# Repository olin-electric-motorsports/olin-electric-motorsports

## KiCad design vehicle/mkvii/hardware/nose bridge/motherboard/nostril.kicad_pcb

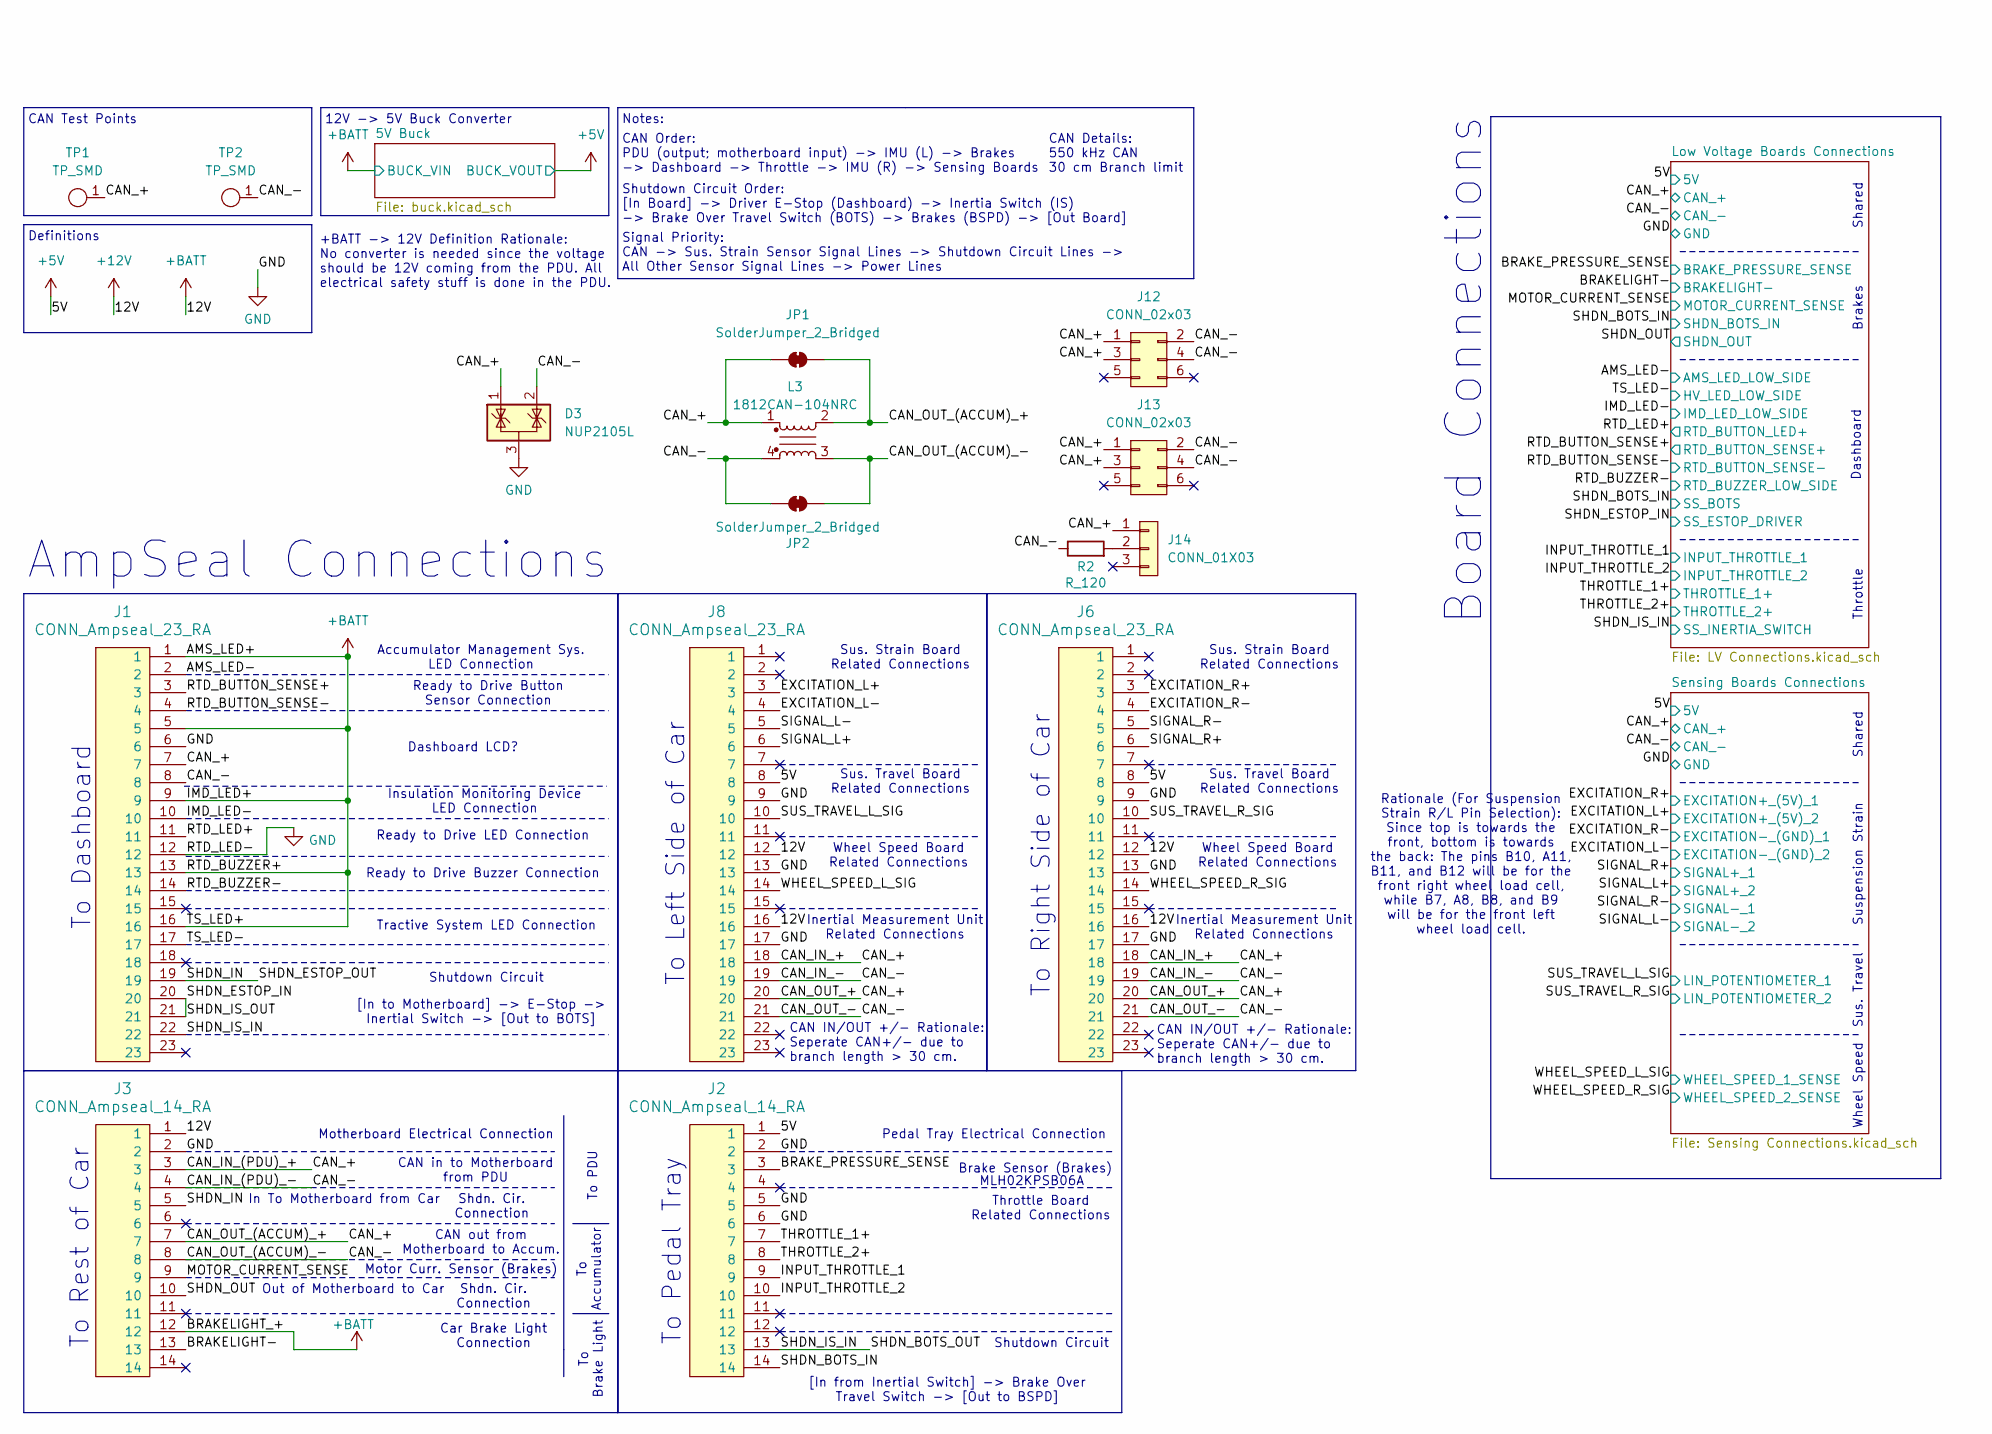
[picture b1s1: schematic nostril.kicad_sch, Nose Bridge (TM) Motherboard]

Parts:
D3: NUP2105L; SOT-23
J1, J6, J8: CONN_Ampseal_23_RA; Ampseal_23_RA; MPN 776087-1
J2, J3: CONN_Ampseal_14_RA; Ampseal_14_RA; MPN 1-776266-1
J12, J13: CONN_02x03; PinHeader_2x03_P2.54mm_Vertical; MPN 10129381-906002BLF
J14: CONN_01X03; PinHeader_1x03_P2.54mm_Vertical; MPN PH1-03-UA
JP1, JP2: SolderJumper_2_Bridged; SolderJumper-2_P1.3mm_Bridged2Bar_Pad1.0x1.5mm
L3: 1812CAN-104NRC; L_CommonModeChoke_Coilcraft_1812CAN
R2: R_120; R_0603; MPN RC0603FR-13120RL
TP1, TP2: TP_SMD; Test_Point_SMD; MPN 5019

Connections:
+5V: J2.1, J6.8, J8.8; also elsewhere on the board
/AMS_LED-: J1.2; also elsewhere on the board
/BRAKELIGHT-: J3.13; also elsewhere on the board
/BRAKE_PRESSURE_SENSE: J2.3; also elsewhere on the board
/CAN_+: D3.1 (K), J1.7, J3.3, J3.7, J6.18, J6.20, J8.18, J8.20, J12.1, J12.3, J13.1, J13.3, J14.1, JP1.1 (A), JP1.2 (B), L3.1, L3.2, TP1.1; also elsewhere on the board
/CAN_-: D3.2 (K), J1.8, J3.4, J3.8, J6.19, J6.21, J8.19, J8.21, J12.2, J12.4, J13.2, J13.4, JP2.1 (A), JP2.2 (B), L3.3, L3.4, R2.1, TP2.1; also elsewhere on the board
/EXCITATION_L+: J8.3; also elsewhere on the board
/EXCITATION_L-: J8.4; also elsewhere on the board
/EXCITATION_R+: J6.3; also elsewhere on the board
/EXCITATION_R-: J6.4; also elsewhere on the board
/IMD_LED-: J1.10; also elsewhere on the board
/INPUT_THROTTLE_1: J2.9; also elsewhere on the board
/INPUT_THROTTLE_2: J2.10; also elsewhere on the board
/MOTOR_CURRENT_SENSE: J3.9; also elsewhere on the board
/RTD_BUTTON_SENSE+: J1.3; also elsewhere on the board
/RTD_BUTTON_SENSE-: J1.4; also elsewhere on the board
/RTD_BUZZER-: J1.14; also elsewhere on the board
/RTD_LED+: J1.11; also elsewhere on the board
/SHDN_BOTS_IN: J2.14; also elsewhere on the board
/SHDN_BOTS_OUT: J1.22, J2.13; also elsewhere on the board
/SHDN_ESTOP_IN: J1.20, J1.21; also elsewhere on the board
/SHDN_ESTOP_OUT: J1.19, J3.5
/SHDN_OUT: J3.10; also elsewhere on the board
/SIGNAL_L+: J8.6; also elsewhere on the board
/SIGNAL_L-: J8.5; also elsewhere on the board
/SIGNAL_R+: J6.6; also elsewhere on the board
/SIGNAL_R-: J6.5; also elsewhere on the board
/SUS_TRAVEL_L_SIG: J8.10; also elsewhere on the board
/SUS_TRAVEL_R_SIG: J6.10; also elsewhere on the board
/THROTTLE_1+: J2.7; also elsewhere on the board
/THROTTLE_2+: J2.8; also elsewhere on the board
/TS_LED-: J1.17; also elsewhere on the board
/WHEEL_SPEED_L_SIG: J8.14; also elsewhere on the board
/WHEEL_SPEED_R_SIG: J6.14; also elsewhere on the board
GND: D3.3 (A), J1.6, J1.12, J2.2, J2.5, J2.6, J3.2, J6.9, J6.13, J6.17, J8.9, J8.13, J8.17; also elsewhere on the board
unnamed: J14.2, R2.2

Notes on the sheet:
Sus. Strain Board Related Connections
Inertial Measurement Unit Related Connections
CAN Order: PDU (output; motherboard input) -> IMU (L) -> Brakes -> Dashboard -> Throttle -> IMU (R) -> Sensing Boards
Shdn. Cir. Connection
Tractive System LED Connection
Insulation Monitoring Device LED Connection
Shutdown Circuit Order: [In Board] -> Driver E-Stop (Dashboard) -> Inertia Switch (IS) -> Brake Over Travel Switch (BOTS) -> Brakes (BSPD) -> [Out Board]
Signal Priority: CAN -> Sus. Strain Sensor Signal Lines -> Shutdown Circuit Lines -> All Other Sensor Signal Lines -> Power Lines
Wheel Speed Board Related Connections
In To Motherboard from Car
Throttle Board Related Connections
Brake Sensor (Brakes)
Shutdown Circuit
Sus. Travel Board Related Connections
[In from Inertial Switch] -> Brake Over Travel Switch -> [Out to BSPD]
Dashboard
CAN Test Points
Motherboard Electrical Connection
Accumulator Management Sys. LED Connection
To Accumulator
CAN Details: 550 kHz CAN 30 cm Branch limit
Wheel Speed
Ready to Drive Buzzer Connection
CAN IN/OUT +/- Rationale: Seperate CAN+/- due to branch length > 30 cm.
To Brake Light
Dashboard LCD?
To Right Side of Car
Definitions
Motor Curr. Sensor (Brakes)
Shared
Ready to Drive Button Sensor Connection
Out of Motherboard to Car
+BATT -> 12V Definition Rationale: No converter is needed since the voltage should be 12V coming from the PDU. All electrical safety stuff is done in the PDU.
MLH02KPSB06A
Throttle
Car Brake Light Connection
To PDU
CAN out from Motherboard to Accum.
12V -> 5V Buck Converter
Notes:

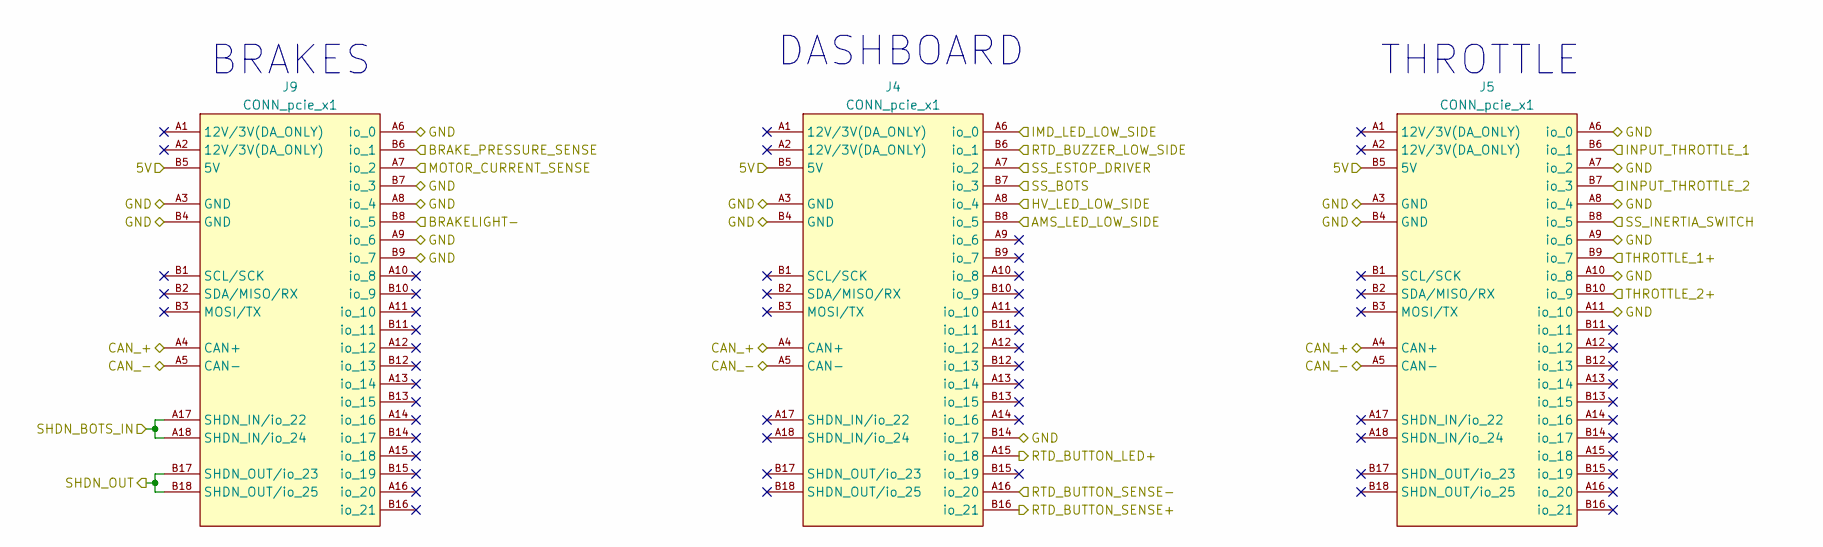
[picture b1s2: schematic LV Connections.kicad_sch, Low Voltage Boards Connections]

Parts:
J4, J5, J9: CONN_pcie_x1; te_pcie_x1_connector

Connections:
+5V: J4.B5 (5V), J5.B5 (5V), J9.B5 (5V); also elsewhere on the board
/AMS_LED-: J4.B8 (io_5); also elsewhere on the board
/BRAKELIGHT-: J9.B8 (io_5); also elsewhere on the board
/BRAKE_PRESSURE_SENSE: J9.B6 (io_1); also elsewhere on the board
/CAN_+: J4.A4 (CAN+), J5.A4 (CAN+), J9.A4 (CAN+); also elsewhere on the board
/CAN_-: J4.A5 (CAN-), J5.A5 (CAN-), J9.A5 (CAN-); also elsewhere on the board
/IMD_LED-: J4.A6 (io_0); also elsewhere on the board
/INPUT_THROTTLE_1: J5.B6 (io_1); also elsewhere on the board
/INPUT_THROTTLE_2: J5.B7 (io_3); also elsewhere on the board
/MOTOR_CURRENT_SENSE: J9.A7 (io_2); also elsewhere on the board
/RTD_BUTTON_SENSE+: J4.B16 (io_21); also elsewhere on the board
/RTD_BUTTON_SENSE-: J4.A16 (io_20); also elsewhere on the board
/RTD_BUZZER-: J4.B6 (io_1); also elsewhere on the board
/RTD_LED+: J4.A15 (io_18); also elsewhere on the board
/SHDN_BOTS_IN: J4.B7 (io_3), J9.A17 (SHDN_IN/io_22), J9.A18 (SHDN_IN/io_24); also elsewhere on the board
/SHDN_BOTS_OUT: J5.B8 (io_5); also elsewhere on the board
/SHDN_ESTOP_IN: J4.A7 (io_2); also elsewhere on the board
/SHDN_OUT: J9.B17 (SHDN_OUT/io_23), J9.B18 (SHDN_OUT/io_25); also elsewhere on the board
/THROTTLE_1+: J5.B9 (io_7); also elsewhere on the board
/THROTTLE_2+: J5.B10 (io_9); also elsewhere on the board
/TS_LED-: J4.A8 (io_4); also elsewhere on the board
GND: J4.A3 (GND), J4.B4 (GND), J4.B14 (io_17), J5.A3 (GND), J5.A6 (io_0), J5.A7 (io_2), J5.A8 (io_4), J5.A9 (io_6), J5.A10 (io_8), J5.A11 (io_10), J5.B4 (GND), J9.A3 (GND), J9.A6 (io_0), J9.A8 (io_4), J9.A9 (io_6), J9.B4 (GND), J9.B7 (io_3), J9.B9 (io_7); also elsewhere on the board

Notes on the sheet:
BRAKES
DASHBOARD
THROTTLE

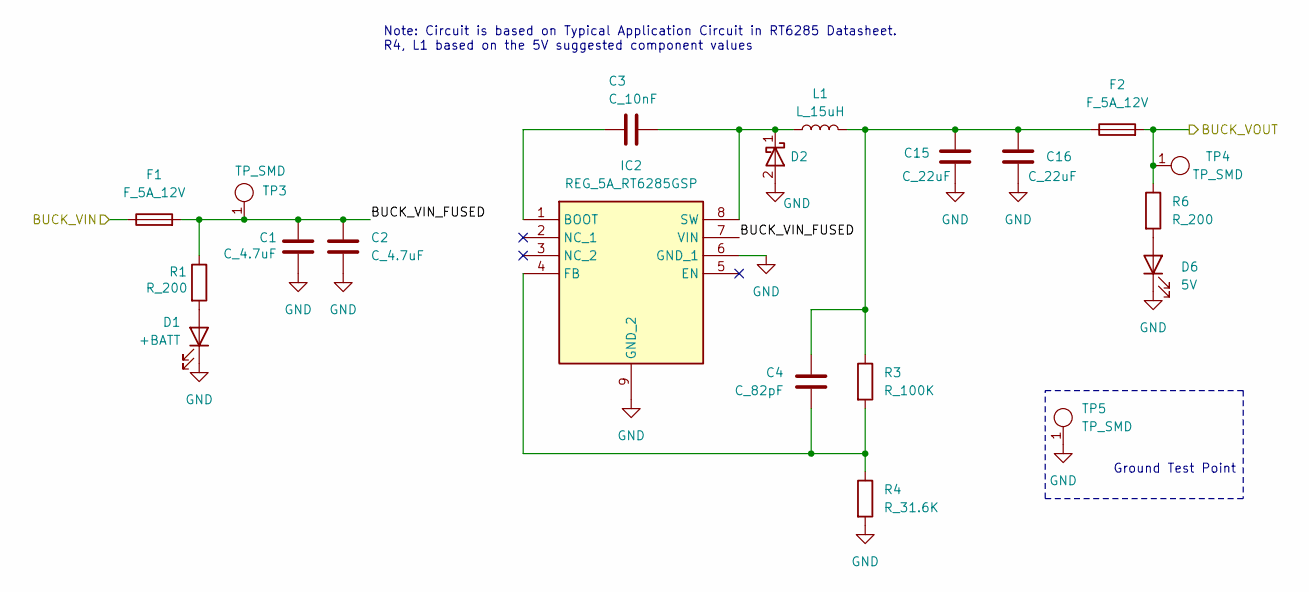
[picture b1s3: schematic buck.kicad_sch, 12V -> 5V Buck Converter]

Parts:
C1, C2: C_4.7uF; C_0603; MPN GRT188R61E475ME13D
C3: C_10nF; C_0603; MPN CL10B103KB8NNNC
C4: C_82pF; C_0603
C15, C16: C_22uF; C_1206_3216Metric; MPN CL31A226KAHNNNE
D1: +BATT; CHIPLED_0805; MPN B1701TW--20P000314U1930
D2: D_Schottky_B550C-13-F; SMC_DIO-M; MPN D_B550C-13-F
D6: 5V; CHIPLED_0805; MPN B1701TW--20P000314U1930
F1, F2: F_5A_12V; Fuse_1210; MPN 0ZCH0050FF2G
IC2: REG_5A_RT6285GSP; SOIC127P600X175-9N; Mouser Part Number 835-RT6285GSP
L1: L_15uH; NR10050T150M; MPN NR10050T150M
R1, R6: R_200; R_0603; MPN RC0603FR-13200RL
R3: R_100K; R_0603; MPN RMCF0603FT100K
R4: R_31.6K; R_0603; MPN RMCF0603FT75K0
TP3, TP4, TP5: TP_SMD; Test_Point_SMD; MPN 5019

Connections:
+5V: F2.2, R6.1, TP4.1; also elsewhere on the board
/5V Buck/BUCK_VIN_FUSED: C1.1, C2.1, F1.2, IC2.7 (VIN), R1.1, TP3.1
GND: C1.2, C2.2, C15.2, C16.2, D1.1 (K), D2.2 (A), D6.1 (K), IC2.6 (GND_1), IC2.9 (GND_2), R4.2, TP5.1; also elsewhere on the board
unnamed: C4.1, C15.1, C16.1, F2.1, L1.2, R3.1
unnamed: D1.2 (A), R1.2
unnamed: C3.1, D2.1 (K), IC2.8 (SW), L1.1
unnamed: D6.2 (A), R6.2
unnamed: C3.2, IC2.1 (BOOT)
unnamed: C4.2, IC2.4 (FB), R3.2, R4.1

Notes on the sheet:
Ground Test Point
Note: Circuit is based on Typical Application Circuit in RT6285 Datasheet. R4, L1 based on the 5V suggested component values

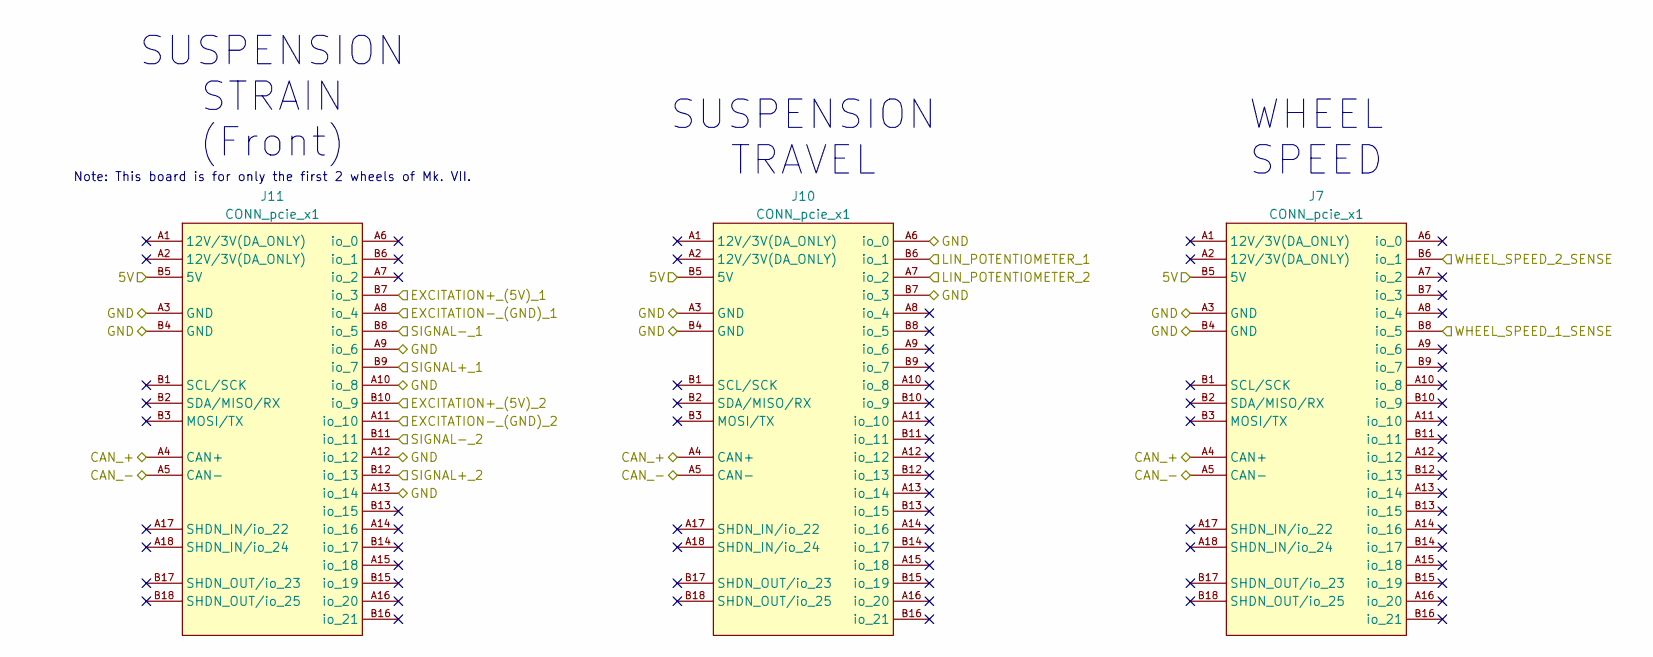
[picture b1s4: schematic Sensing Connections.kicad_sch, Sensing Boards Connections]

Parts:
J7, J10, J11: CONN_pcie_x1; te_pcie_x1_connector

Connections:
+5V: J7.B5 (5V), J10.B5 (5V), J11.B5 (5V); also elsewhere on the board
/CAN_+: J7.A4 (CAN+), J10.A4 (CAN+), J11.A4 (CAN+); also elsewhere on the board
/CAN_-: J7.A5 (CAN-), J10.A5 (CAN-), J11.A5 (CAN-); also elsewhere on the board
/EXCITATION_L+: J11.B10 (io_9); also elsewhere on the board
/EXCITATION_L-: J11.A11 (io_10); also elsewhere on the board
/EXCITATION_R+: J11.B7 (io_3); also elsewhere on the board
/EXCITATION_R-: J11.A8 (io_4); also elsewhere on the board
/SIGNAL_L+: J11.B12 (io_13); also elsewhere on the board
/SIGNAL_L-: J11.B11 (io_11); also elsewhere on the board
/SIGNAL_R+: J11.B9 (io_7); also elsewhere on the board
/SIGNAL_R-: J11.B8 (io_5); also elsewhere on the board
/SUS_TRAVEL_L_SIG: J10.B6 (io_1); also elsewhere on the board
/SUS_TRAVEL_R_SIG: J10.A7 (io_2); also elsewhere on the board
/WHEEL_SPEED_L_SIG: J7.B8 (io_5); also elsewhere on the board
/WHEEL_SPEED_R_SIG: J7.B6 (io_1); also elsewhere on the board
GND: J7.A3 (GND), J7.B4 (GND), J10.A3 (GND), J10.A6 (io_0), J10.B4 (GND), J10.B7 (io_3), J11.A3 (GND), J11.A9 (io_6), J11.A10 (io_8), J11.A12 (io_12), J11.A13 (io_14), J11.B4 (GND); also elsewhere on the board

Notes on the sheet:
SUSPENSION TRAVEL
SUSPENSION STRAIN (Front)
Note: This board is for only the first 2 wheels of Mk. VII.
WHEEL SPEED

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
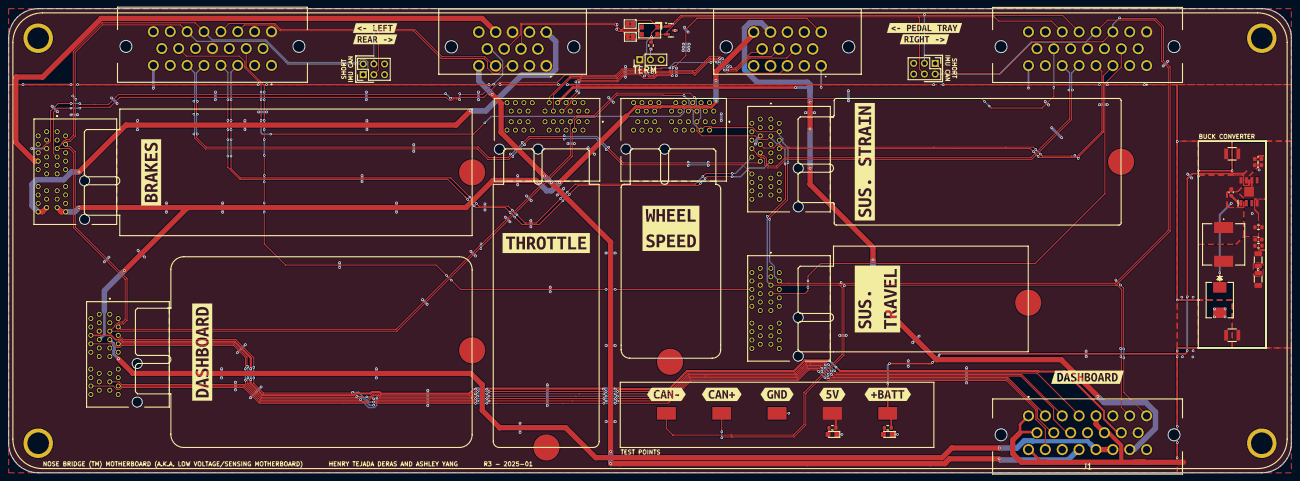
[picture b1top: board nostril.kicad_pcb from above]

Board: 2 copper layers, 304.0 x 110.0 mm, 64 parts (1 on the bottom side), 44 nets.

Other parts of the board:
REFe: MountingHole_440_Keystone_4939
REFe#2, REFe#3, REFe#4, REFe#5, REFe#6: MountingHole_440_Keystone_4939
kibuzzard-675B44D9: G***; kibuzzard-675B44D9
kibuzzard-675B44FA: G***; kibuzzard-675B44FA
kibuzzard-675B44FE: G***; kibuzzard-675B44FE
kibuzzard-675B459C: G***; kibuzzard-675B459C
kibuzzard-675B4597: G***; kibuzzard-675B4597
kibuzzard-676F5A21: G***; kibuzzard-676F5A21
kibuzzard-6740CE06: G***; kibuzzard-6740CE06
kibuzzard-6740CF1B: G***; kibuzzard-6740CF1B
kibuzzard-6740CF16: G***; kibuzzard-6740CF16
kibuzzard-6740CF20: G***; kibuzzard-6740CF20
kibuzzard-6743B4BF: G***; kibuzzard-6743B4BF
kibuzzard-6743B4EA: G***; kibuzzard-6743B4EA
kibuzzard-6743B5D1: G***; kibuzzard-6743B5D1
kibuzzard-6743B5DC: G***; kibuzzard-6743B5DC
kibuzzard-6755A54C: G***; kibuzzard-6755A54C
kibuzzard-6755A536: G***; kibuzzard-6755A536
kibuzzard-6744832F: G***; kibuzzard-6744832F

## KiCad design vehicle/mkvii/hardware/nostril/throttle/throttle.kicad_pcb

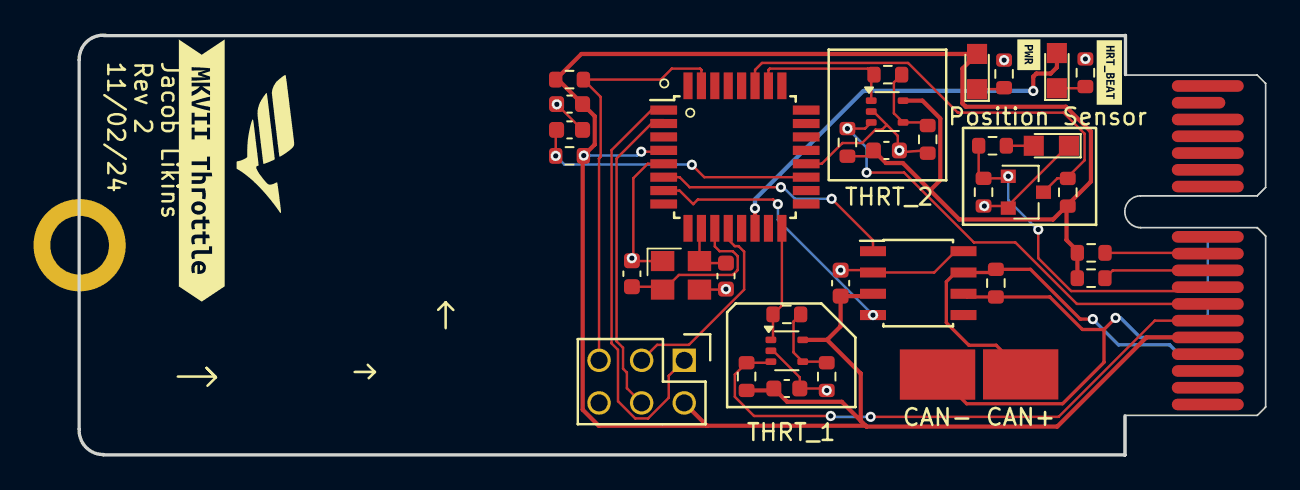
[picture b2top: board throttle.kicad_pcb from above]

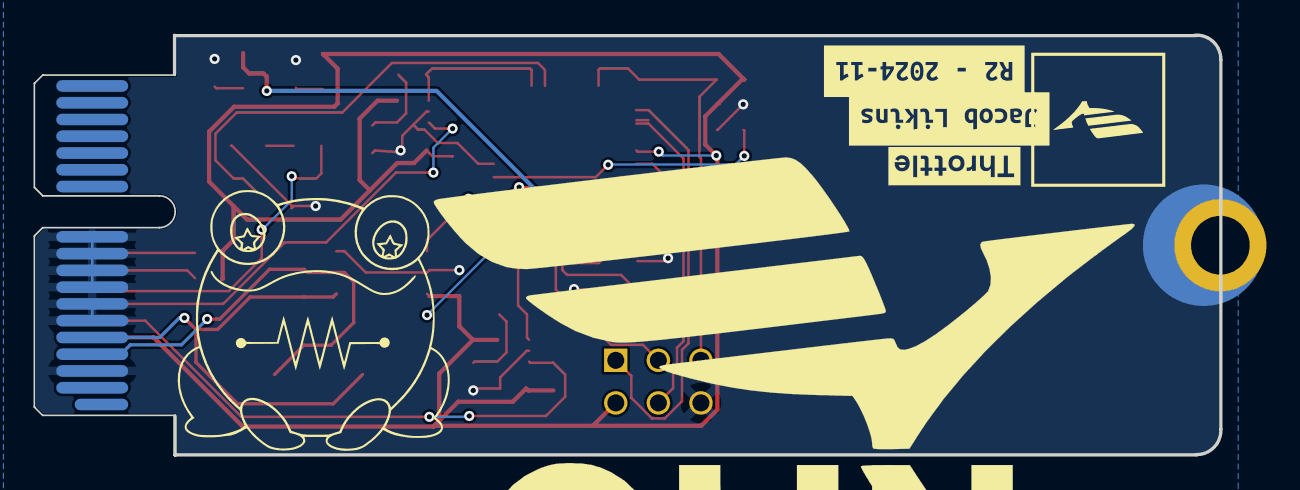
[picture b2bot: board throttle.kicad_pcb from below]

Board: 2 copper layers, 70.8 x 25.0 mm, 44 parts (4 on the bottom side), 27 nets.

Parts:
C1, C2, C3, C7: 0.1uF; C_0603
C4: C_100pF; C_0603
C5, C6: C_30pF; C_0603
CAN+: CANH1; Test_Point_SMD
CAN-: CANL1; Test_Point_SMD
D1: LED_BLUE; CHIPLED_0805
D2: LED_AMBER; CHIPLED_0805
D3: LED_WHITE; CHIPLED_0805
J2: CONN_02x03; Pin_Header_Straight_2x03
J4: CONN_pcie_x1; pcie_x1
Q1: SSM3K333R; SOT-23F
QR*****: hw.oem.to/6_THROTTLE_1; QR_6_THROTTLE_1
R1, R4: R_1M; R_0603
R2, R5, R11: R_0; R_0603
R3, R6: R_2.2K; R_0603
R7: 3KR; R_0603
R8: R_100K; R_0603
R9, R13, R17: R_10K; R_0603
R12: R_100; R_0603
R14: R_120_DNP; R_0603
R15, R16: 1KR; R_0603
U1, U2: MCP6001; SOT-353_SC-70-5
U3: ATMEGA16M1; TQFP-32_7x7mm_Pitch0.8mm
U4: MAX33011EASA; SOIC-8_3.9x4.9mm_Pitch1.27mm_OEM
U$2: M.2_Mount
Y1: Crystal_16MHz_18pF; Crystal_TXC7M
kibuzzard-63D83A03: G***; kibuzzard-63D83A03
kibuzzard-672E9653: G***; kibuzzard-672E9653
kibuzzard-672E9698: G***; kibuzzard-672E9698
kibuzzard-6726AB29: G***; kibuzzard-6726AB29
kibuzzard-6726AB44: G***; kibuzzard-6726AB44
kibuzzard-6726AB56: G***; kibuzzard-6726AB56

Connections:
+5V: C1.1, C2.1, C3.1, C7.1, D3.2 (A), J2.2, J4.B5 (5V), R1.1, R4.1, R9.1, R11.1, R12.1, R13.1, R17.1, U1.5 (V+), U2.5 (V+), U3.4 (VCC), U4.3 (VDD)
/ Shutdown Sense Inertial Switch/SS_INERTIA_OUTPUT: Q1.3 (D), R9.2, U3.27 ((PCINT6/ADC7/PSCOUT1B)PB6)
/INPUT_THROTTLE_1: J4.B6 (io_1), R1.2, U1.3 (+)
/INPUT_THROTTLE_2: J4.B7 (io_3), R4.2, U2.3 (+)
/Microcontroller/CAN_+: CAN+.1, J4.A4 (CAN+), R14.1, U4.7 (CANH)
/Microcontroller/CAN_-: CAN-.1, J4.A5 (CAN-), R14.2, U4.6 (CANL)
/Microcontroller/CAN_RX: U3.7 ((PCINT11/T1/ICP1B/RXCAN)PC3), U4.4 (RXD)
/Microcontroller/CAN_TX: U3.6 ((PCINT10/T0/TXCAN)PC2), U4.1 (TXD)
/Microcontroller/Heartbeat: D2.2 (A), U3.14 ((PCINT22/ADC3/INT0/ACMPN2)PD6)
/Microcontroller/MISO: J2.1, U3.1 ((PCINT18/PSCIN2/OC1A/MISO_A)PD2)
/Microcontroller/MOSI: J2.4, U3.2 ((PCINT19/TXD/TXLIN/OC0A/~SS/MOSI_A)PD3)
/Microcontroller/OUTPUT_THROTTLE_1: R2.1, U1.1, U3.16 ((PCINT2/ADC5/INT1/ACMPN0)PB2)
/Microcontroller/OUTPUT_THROTTLE_2: R5.1, U2.1, U3.26 ((PCINT5/ADC6/INT2/ACMPN1/AMP2-)PB5)
/Microcontroller/RESET: J2.5, R13.2, U3.31 ((PCINT24/OCD/~RESET)PE0)
/Microcontroller/SCK: J2.3, U3.12 ((PCINT20/ADC1/RXD/RXLIN/ICP1A/SCK_A)PD4)
/SS_INERTIA_SWITCH: J4.B8 (io_5), Q1.1 (G), R7.2, R8.1
/THROTTLE_1+: J4.B9 (io_7), R17.2
/THROTTLE_2+: J4.B10 (io_9), R11.2
GND: C1.2, C2.2, C3.2, C4.2, C5.2, C6.2, C7.2, D1.1 (K), J2.6, J4.A3 (GND), J4.A6 (io_0), J4.A7 (io_2), J4.A8 (io_4), J4.A9 (io_6), J4.A10 (io_8), J4.A11 (io_10), J4.B4 (GND), Q1.2 (S), R3.2, R6.2, R8.2, R15.2, R16.2, U1.2 (V-), U2.2 (V-), U3.5 (GND), U3.20 (AGND), U4.2 (VSS), U4.8 (STBY), U$2.1, Y1.2, Y1.4
unnamed: D1.2 (A), R7.1
unnamed: D2.1 (K), R15.1
unnamed: D3.1 (K), R16.1
unnamed: R2.2, R3.1, U1.4 (-)
unnamed: R5.2, R6.1, U2.4 (-)
unnamed: C6.1, U3.10 ((PCINT25/OC0B/XTAL1)PE1), Y1.3
unnamed: C5.1, U3.11 ((PCINT26/ADC0/XTAL2)PE2), Y1.1
unnamed: C4.1, R12.2, U3.19 (AVCC)

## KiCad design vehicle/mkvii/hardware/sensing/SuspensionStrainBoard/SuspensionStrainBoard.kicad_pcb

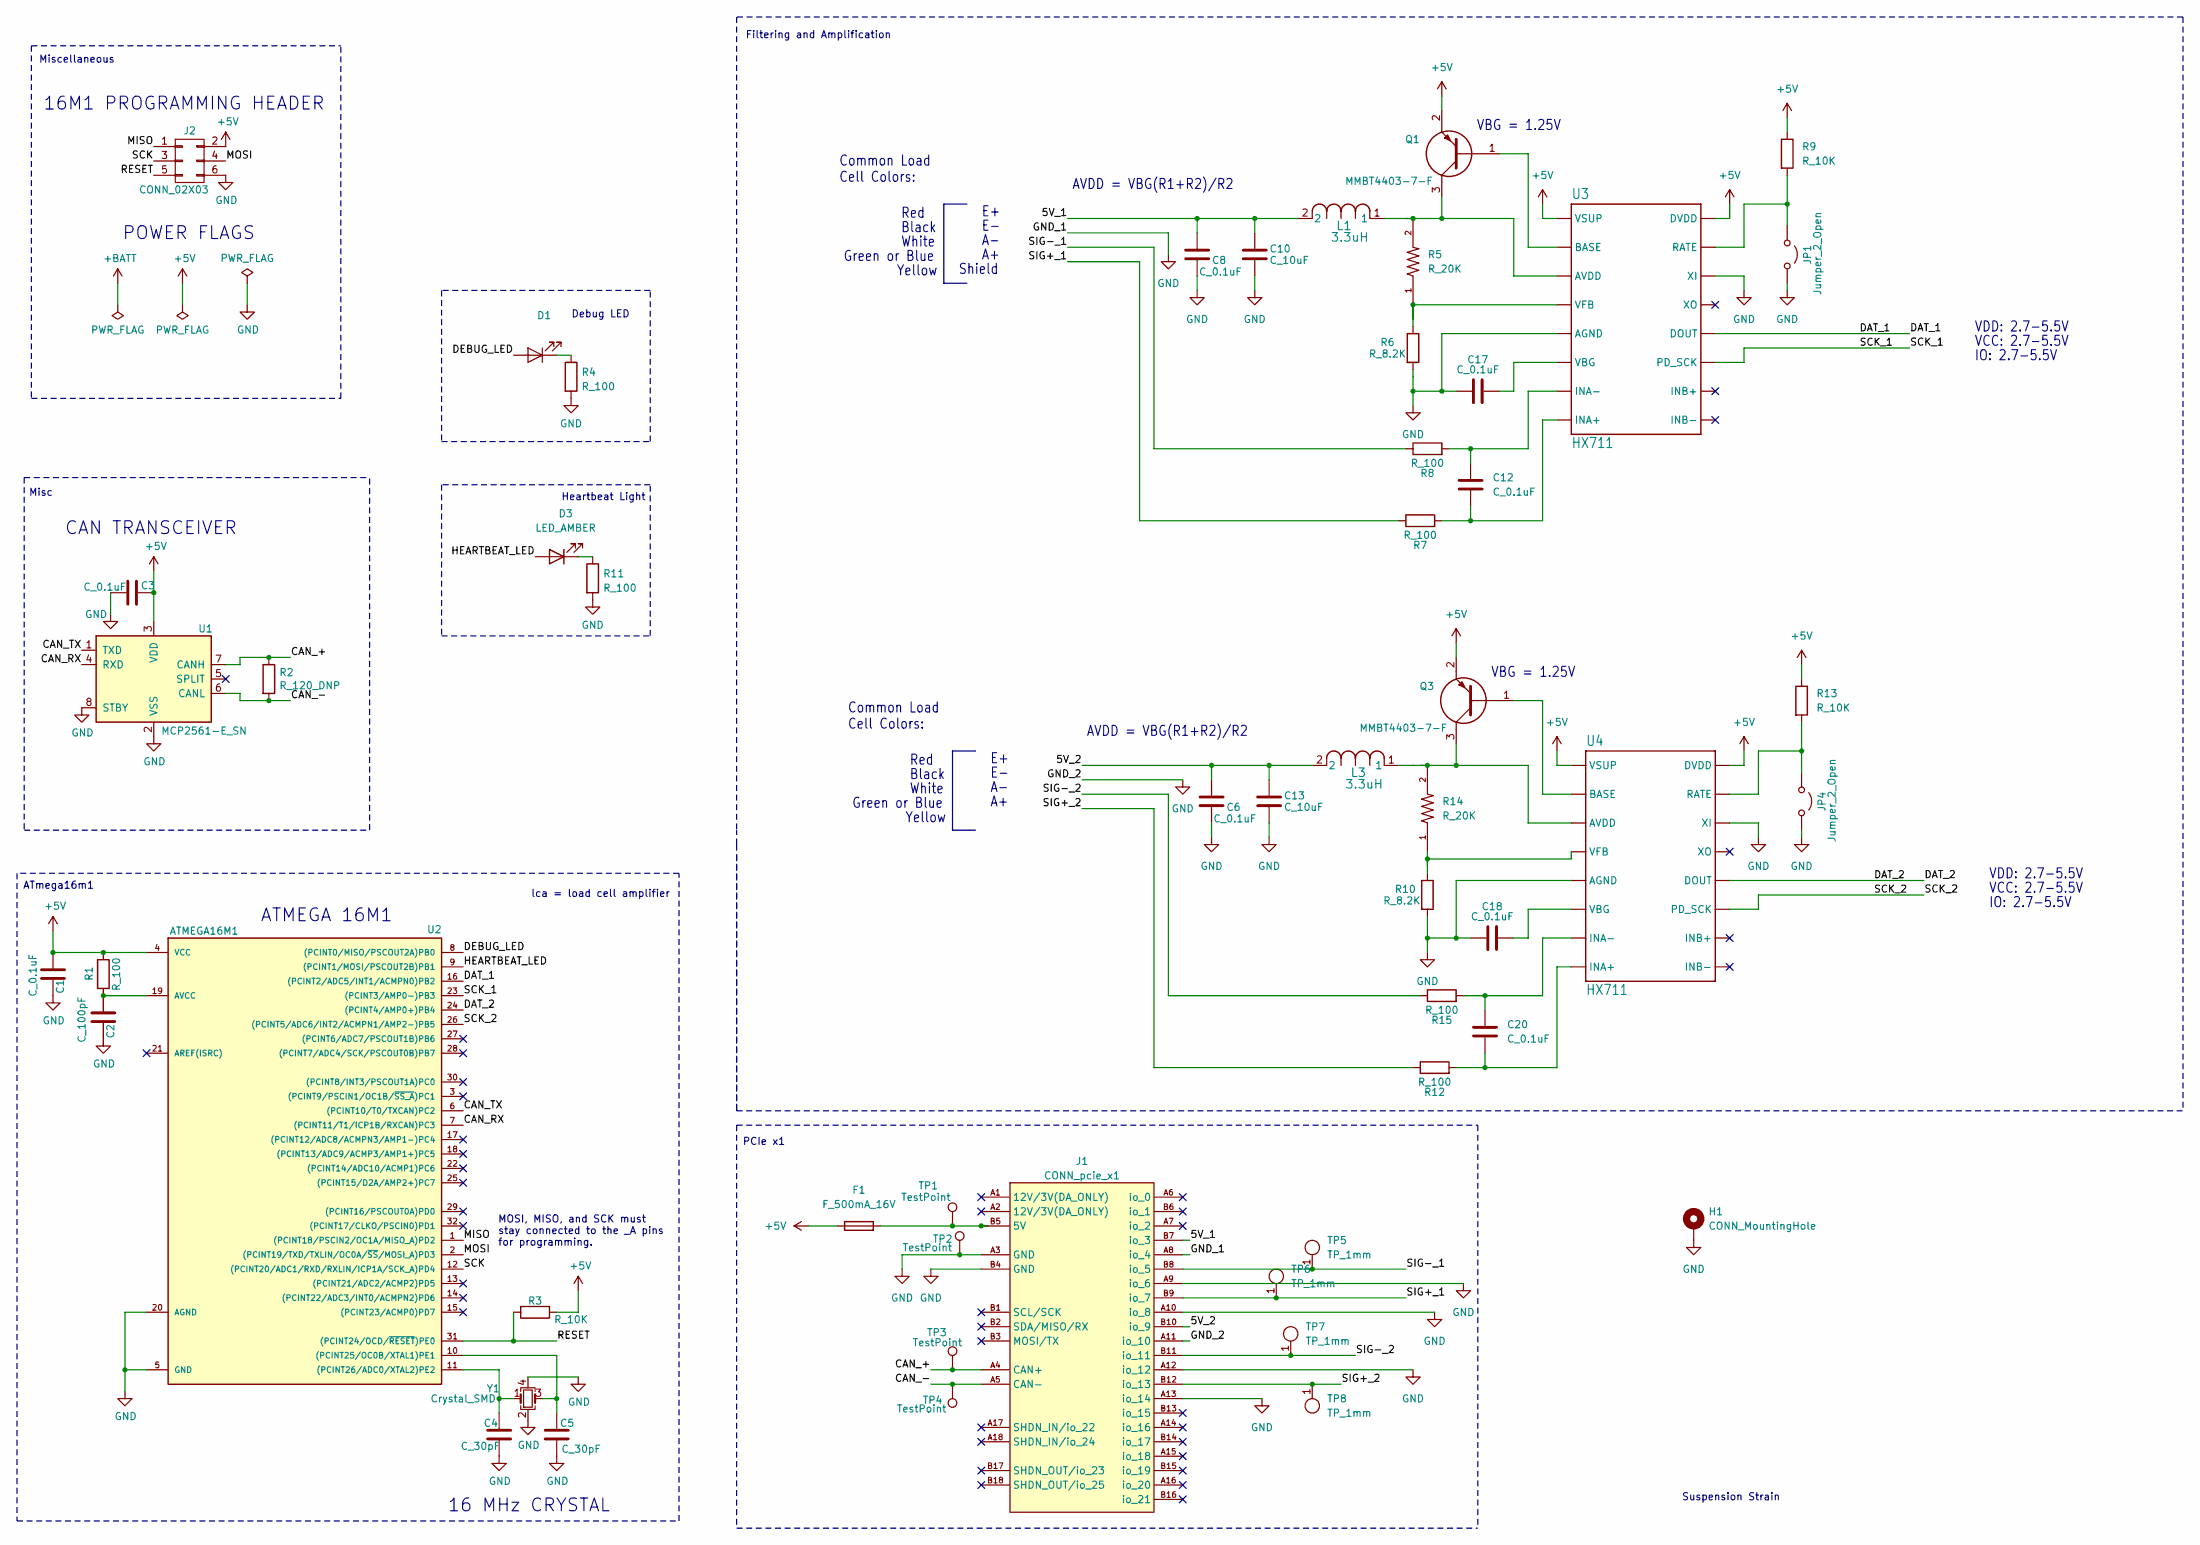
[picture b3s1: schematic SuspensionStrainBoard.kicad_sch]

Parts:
C1, C3: C_0.1uF; C_0603; MPN 478-3352-1-ND
C2: C_100pF; C_0603; MPN 732-7852-1-ND
C4, C5: C_30pF; C_0603; MPN 1276-1130-1-ND
C6, C8, C12, C17, C18, C20: C_0.1uF; C_0603; MPN CL10B104KB8NNWC
C10, C13: C_10uF; C_0603; MPN LMK107BBJ106KALT
D1: LED_0805; CHIPLED_0805; MPN 475-1410-1-ND
D3: LED_AMBER; CHIPLED_0805
F1: F_500mA_16V; Fuse_1210; MPN 0ZCH0050FF2G
H1: CONN_MountingHole; PCIe_Mount
J1: CONN_pcie_x1; pcie_x1
J2: CONN_02X03; PinHeader_2x03_P2.54mm_Vertical; MPN 609-3234-ND
JP1, JP4: Jumper_2_Open; SolderJumper-2_P1.3mm_Open_Pad1.0x1.5mm
L1, L3: 3.3uH; 0805
Q1, Q3: MMBT4403-7-F; SOT23-3; Manufacturer_Part_Number MMBT4403-7-F
R1, R4, R11: R_100; R_0603; MPN RNCP0805FTD100RCT-ND
R2: R_120_DNP; R_0603; MPN 667-ERJ-6ENF1200V
R3: R_10K; R_0603; MPN CRS0805-FX-1002ELFCT-ND
R5, R14: R_20K; R_0603; Voltage_Rating 50 V; Tolerance 1%
R6, R10: R_8.2K; R_0603
R7, R8, R12, R15: R_100; R_0603; MPN RMCF0603FT100R
R9, R13: R_10K; R_0603; MPN RMCF0603FT10K0
TP1, TP2, TP3, TP4: TestPoint; Test_Point_SMD
TP5, TP6, TP7, TP8: TP_1mm; TestPoint_Pad_D1mm
U1: MCP2561-E_SN; SOIC-8_3.9x4.9mm_Pitch1.27mm_OEM; MPN MCP2561-E/SN-ND
U2: ATMEGA16M1; TQFP-32_7x7mm_Pitch0.8mm; MPN ATMEGA16M1-AU-ND
U3, U4: HX711; SO16
Y1: Crystal_SMD; Crystal_TXC7M; MPN 887-1125-1-ND

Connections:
+5V: C1.1, C3.1, F1.1, J2.2, Q1.2, Q3.2, R1.1, R3.1, R9.1, R13.1, U1.3 (VDD), U2.4 (VCC), U3.1 (VSUP), U3.16 (DVDD), U4.1 (VSUP), U4.16 (DVDD); also elsewhere on the board
/5V_1: C8.1, C10.1, J1.B7 (io_3), L1.2
/5V_2: C6.1, C13.1, J1.B10 (io_9), L3.2
/CAN_+: J1.A4 (CAN+), R2.1, TP3.1, U1.7 (CANH)
/CAN_-: J1.A5 (CAN-), R2.2, TP4.1, U1.6 (CANL)
/CAN_RX: U1.4 (RXD), U2.7 ((PCINT11/T1/ICP1B/RXCAN)PC3)
/CAN_TX: U1.1 (TXD), U2.6 ((PCINT10/T0/TXCAN)PC2)
/DAT_1: U2.16 ((PCINT2/ADC5/INT1/ACMPN0)PB2), U3.12 (DOUT)
/DAT_2: U2.24 ((PCINT4/AMP0+)PB4), U4.12 (DOUT)
/DEBUG_LED: D1.2 (A), U2.8 ((PCINT0/MISO/PSCOUT2A)PB0)
/HEARTBEAT_LED: D3.2 (A), U2.9 ((PCINT1/MOSI/PSCOUT2B)PB1)
/MISO: J2.1, U2.1 ((PCINT18/PSCIN2/OC1A/MISO_A)PD2)
/MOSI: J2.4, U2.2 ((PCINT19/TXD/TXLIN/OC0A/~SS/MOSI_A)PD3)
/RESET: J2.5, R3.2, U2.31 ((PCINT24/OCD/~RESET)PE0)
/SCK: J2.3, U2.12 ((PCINT20/ADC1/RXD/RXLIN/ICP1A/SCK_A)PD4)
/SCK_1: U2.23 ((PCINT3/AMP0-)PB3), U3.11 (PD_SCK)
/SCK_2: U2.26 ((PCINT5/ADC6/INT2/ACMPN1/AMP2-)PB5), U4.11 (PD_SCK)
/SIG+_1: J1.B9 (io_7), R7.1, TP6.1
/SIG+_2: J1.B12 (io_13), R12.1, TP8.1
/SIG-_1: J1.B8 (io_5), R8.1, TP5.1
/SIG-_2: J1.B11 (io_11), R15.1, TP7.1
GND: C1.2, C2.2, C3.2, C4.2, C5.2, C6.2, C8.2, C10.2, C13.2, C17.1, C18.1, H1.1, J1.A3 (GND), J1.A8 (io_4), J1.A9 (io_6), J1.A10 (io_8), J1.A11 (io_10), J1.A12 (io_12), J1.A13 (io_14), J1.B4 (GND), J2.6, JP1.2 (B), JP4.2 (B), R4.2, R6.2, R10.2, R11.2, TP2.1, U1.2 (VSS), U1.8 (STBY), U2.5 (GND), U2.20 (AGND), U3.5 (AGND), U3.14 (XI), U4.5 (AGND), U4.14 (XI), Y1.2, Y1.4; also elsewhere on the board
unnamed: D1.1 (K), R4.1
unnamed: D3.1 (K), R11.1
unnamed: F1.2, J1.B5 (5V), TP1.1
unnamed: JP1.1 (A), R9.2, U3.15 (RATE)
unnamed: JP4.1 (A), R13.2, U4.15 (RATE)
unnamed: C5.1, U2.10 ((PCINT25/OC0B/XTAL1)PE1), Y1.3
unnamed: C4.1, U2.11 ((PCINT26/ADC0/XTAL2)PE2), Y1.1
unnamed: C2.1, R1.2, U2.19 (AVCC)
unnamed: L1.1, Q1.3, R5.2, U3.3 (AVDD)
unnamed: Q1.1, U3.2 (BASE)
unnamed: C12.2, R7.2, U3.8 (INA+)
unnamed: C12.1, R8.2, U3.7 (INA-)
unnamed: C17.2, U3.6 (VBG)
unnamed: R5.1, R6.1, U3.4 (VFB)
unnamed: L3.1, Q3.3, R14.2, U4.3 (AVDD)
unnamed: Q3.1, U4.2 (BASE)
unnamed: C20.2, R12.2, U4.8 (INA+)
unnamed: C20.1, R15.2, U4.7 (INA-)
unnamed: C18.2, U4.6 (VBG)
unnamed: R10.1, R14.1, U4.4 (VFB)

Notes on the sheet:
VDD: 2.7-5.5V
ATmega16m1
PCIe x1
Red
VBG = 1.25V
POWER FLAGS
Miscellaneous
Yellow
Black
Misc
Green or Blue
IO: 2.7-5.5V
lca = load cell amplifier
Debug LED
CAN TRANSCEIVER
Suspension Strain
VCC: 2.7-5.5V
White
Filtering and Amplification
AVDD = VBG(R1+R2)/R2
16 MHz CRYSTAL
ATMEGA 16M1
Common Load Cell Colors:
Shield
MOSI, MISO, and SCK must stay connected to the _A pins for programming.
16M1 PROGRAMMING HEADER
Heartbeat Light

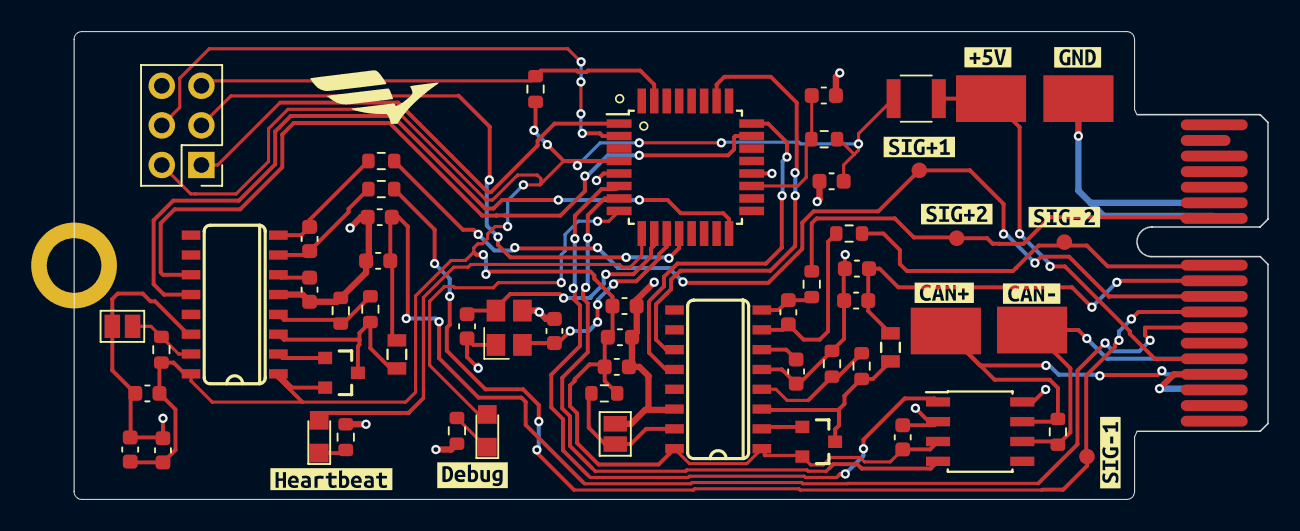
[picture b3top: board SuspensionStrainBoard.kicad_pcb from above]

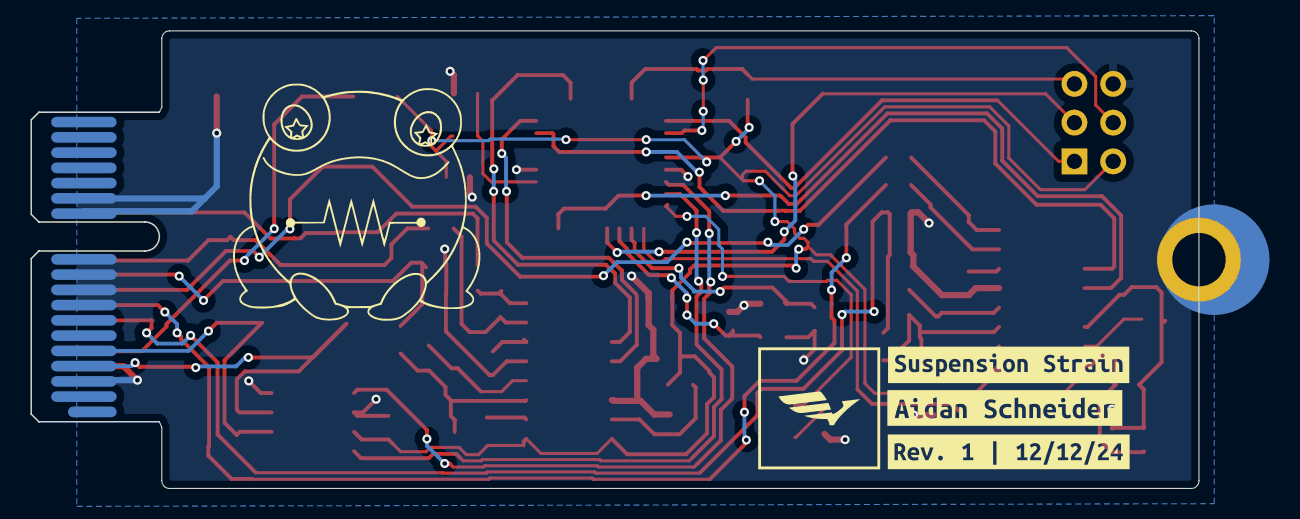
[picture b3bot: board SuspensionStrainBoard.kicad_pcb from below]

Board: 2 copper layers, 76.6 x 30.0 mm, 72 parts (3 on the bottom side), 42 nets.

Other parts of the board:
C7, C9, C14, C15: C_0.1uF; C_0603
C11, C16: C_10uF; C_0603
kibuzzard-675B7DD6: G***; kibuzzard-675B7DD6
kibuzzard-675B7E00: G***; kibuzzard-675B7E00
kibuzzard-675B7E37: G***; kibuzzard-675B7E37
kibuzzard-675B7E48: G***; kibuzzard-675B7E48
kibuzzard-675B7E55: G***; kibuzzard-675B7E55
kibuzzard-675B7E63: G***; kibuzzard-675B7E63
kibuzzard-675B7E95: G***; kibuzzard-675B7E95
kibuzzard-675B7EA0: G***; kibuzzard-675B7EA0
kibuzzard-675B803A: G***; kibuzzard-675B803A
kibuzzard-675B8016: G***; kibuzzard-675B8016
kibuzzard-67840F31: G***; kibuzzard-67840F31
kibuzzard-67840FED: G***; kibuzzard-67840FED
kibuzzard-67841015: G***; kibuzzard-67841015

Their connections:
+5V: C7.1, C9.1, C11.1, C14.1, C15.1, C16.1; also elsewhere on the board
GND: C7.2, C9.2, C11.2, C14.2, C15.2, C16.2; also elsewhere on the board
